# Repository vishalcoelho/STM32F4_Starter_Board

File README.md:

# STM32F4_Starter_Board
KiCAD 9 project for the STM32F405RGT6 starter board

---

I have been following [Phil's Lab Tutorial](https://www.youtube.com/watch?v=C7-8nUU6e3E) on designing your first PCB in KiCad and using JLCPCB as the assembly house. I did the entire project in KiCAD 9, which differs slightly from the video, and ended up taking notes :memo: and screenshots :camera: along the way, which I put into a four part blog:

1. :triangular_ruler: [First STM32 PCB Design in KiCad and JLCPCB Assembly: Part I - Schematic Layout](https://vishalcoelho.github.io/blog/kicad/pcb-design/kicad-stm32-usb-pcb-design-jlcpcb-assy-part-1/)
2. :world_map: [First STM32 PCB Design in KiCad and JLCPCB Assembly: Part II - Board Layout](https://vishalcoelho.github.io/blog/kicad/pcb-design/kicad-stm32-usb-pcb-design-jlcpcb-assy-part-2/)
3. :traffic_light: [First STM32 PCB Design in KiCad and JLCPCB Assembly: Part III - Routing](https://vishalcoelho.github.io/blog/kicad/pcb-design/kicad-stm32-usb-pcb-design-jlcpcb-assy-part-3/)
4. :factory: [First STM32 PCB Design in KiCad and JLCPCB Assembly: Part IV - Manufacturing and Assembly](https://vishalcoelho.github.io/blog/kicad/pcb-design/kicad-stm32-usb-pcb-design-jlcpcb-assy-part-4/)

> :pray: Apologies if the blog doesn't read like a normal tutorial, they really were notes I took for later reference.

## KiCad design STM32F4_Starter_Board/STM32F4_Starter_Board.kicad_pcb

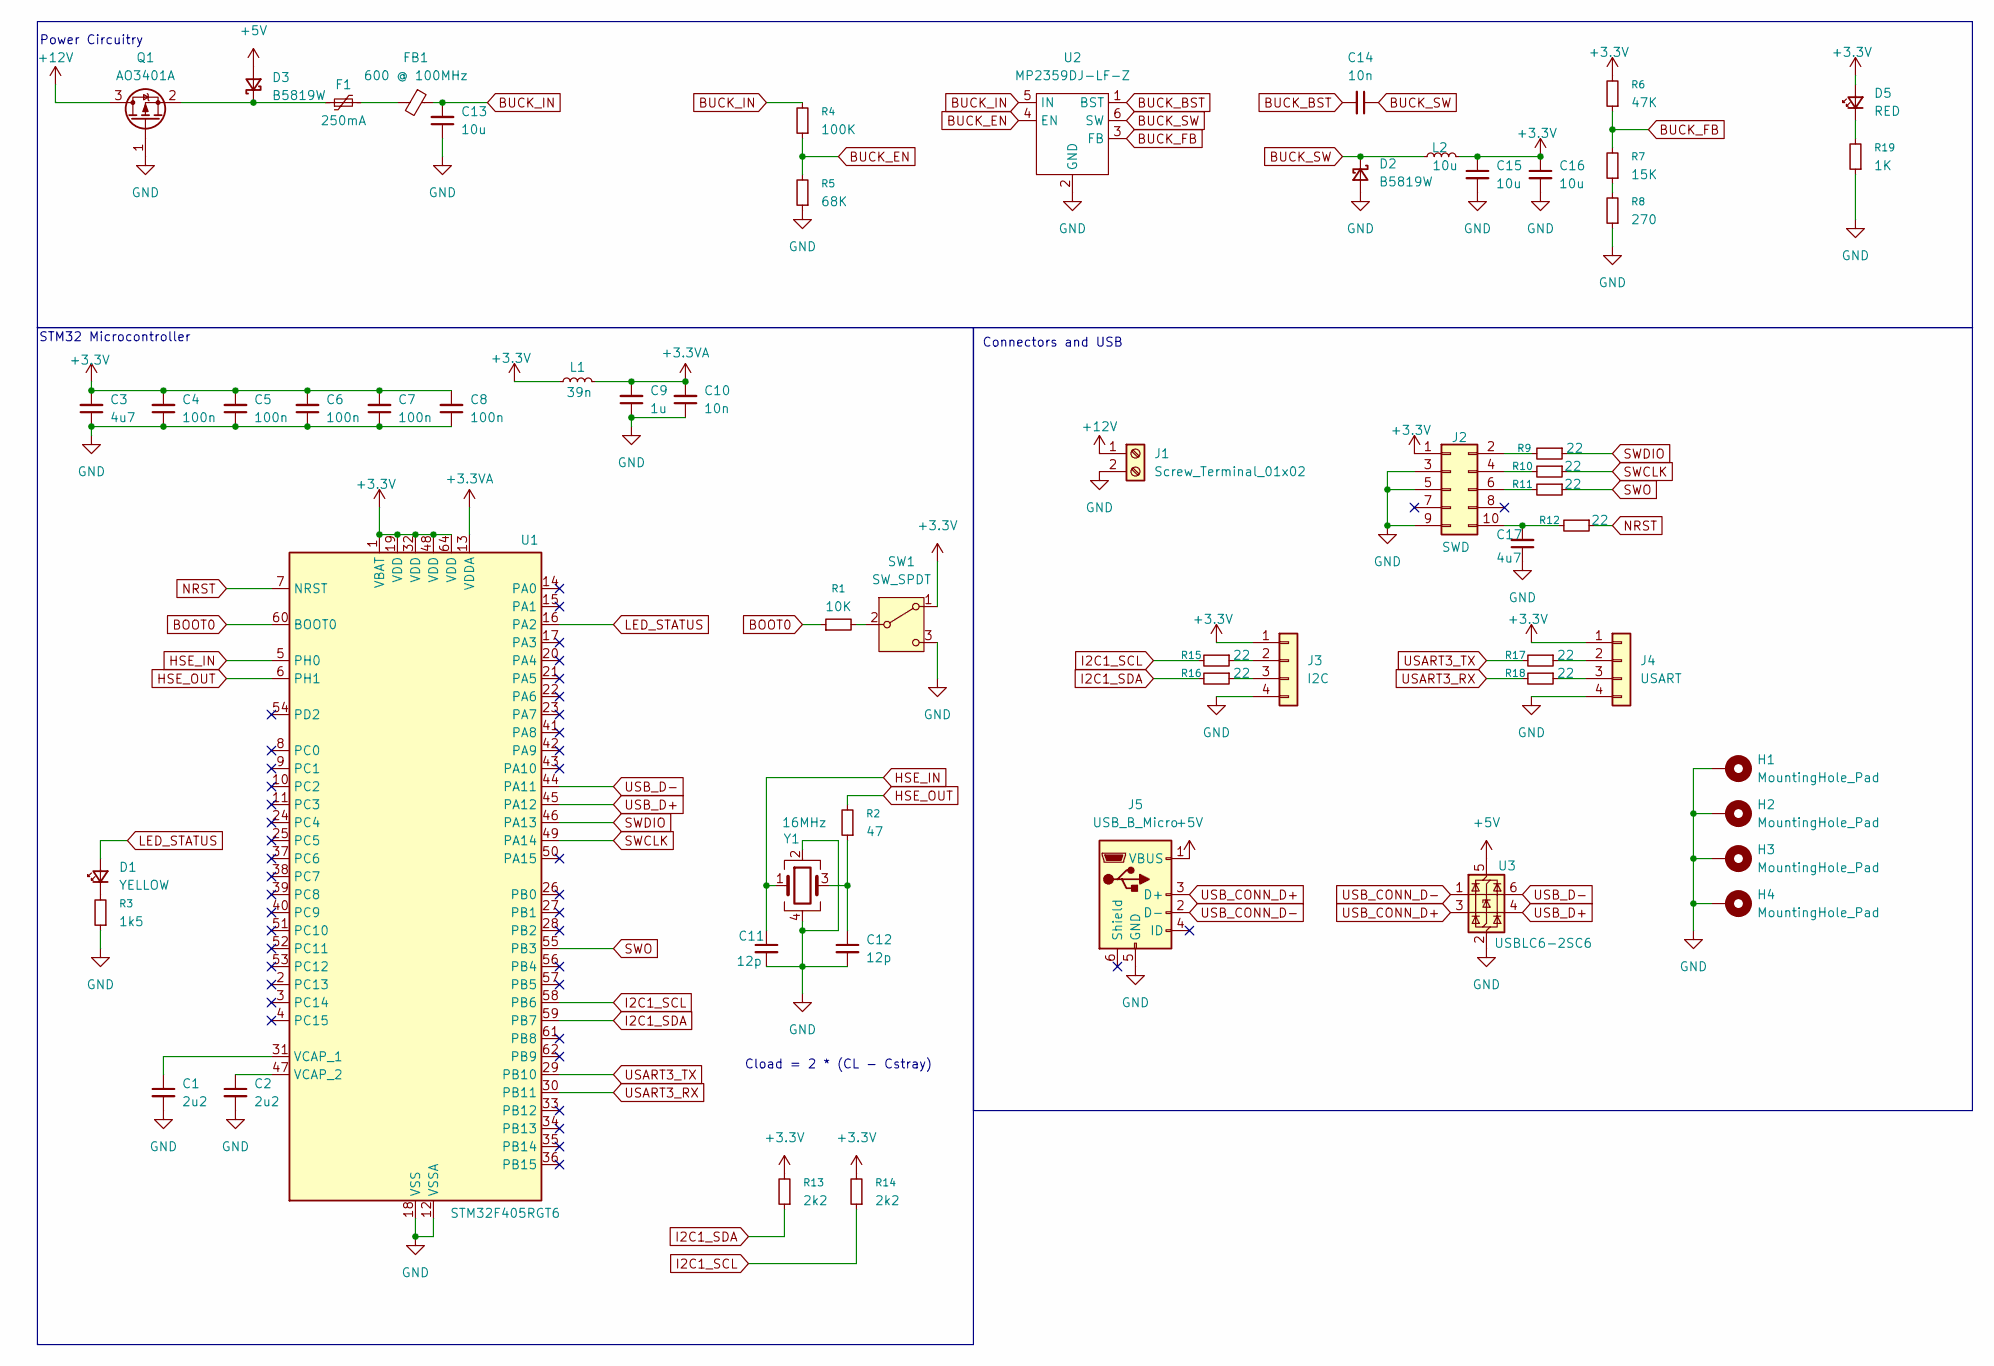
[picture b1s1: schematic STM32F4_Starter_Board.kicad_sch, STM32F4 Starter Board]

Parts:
C1, C2: 2u2; C_0603_1608Metric; JLCPCB Part # C23630
C3, C17: 4u7; C_0603_1608Metric; JLCPCB Part # C19666
C4, C5, C6, C7, C8: 100n; C_0402_1005Metric; JLCPCB Part # C1525
C9: 1u; C_0402_1005Metric; JLCPCB Part # C52923
C10: 10n; C_0603_1608Metric; JLCPCB Part # C57112
C11, C12: 12p; C_0402_1005Metric; JLCPCB Part # C1547
C13, C15, C16: 10u; D_1206_3216Metric; JLCPCB Part # C13585
C14: 10n; D_1206_3216Metric; JLCPCB Part # C1846
D1: YELLOW; LED_0603_1608Metric; JLCPCB Part # C2290
D2, D3: B5819W; D_SOD-123; JLCPCB Part # C8598
D5: RED; LED_0603_1608Metric; JLCPCB Part # C2286
F1: 250mA; Fuse_1206_3216Metric; JLCPCB Part # C83557
FB1: 600 @ 100MHz; L_0805_2012Metric; JLCPCB Part # C1017
H1, H2, H3, H4: MountingHole_Pad; MountingHole_4.3mm_M4_Pad_Via
J1: Screw_Terminal_01x02; TerminalBlock_Phoenix_PT-1,5-2-3.5-H_1x02_P3.50mm_Horizontal; JLCPCB Part # C415432
J2: SWD; PinHeader_2x05_P1.27mm_Vertical_SMD; JLCPCB Part # C4943297
J3: I2C; Molex_PicoBlade_53048-0410_1x04_P1.25mm_Horizontal; JLCPCB Part # C588275
J4: USART; Molex_PicoBlade_53048-0410_1x04_P1.25mm_Horizontal; JLCPCB Part # C588275
J5: USB_B_Micro; USB_Micro-B_Molex_47346-0001; JLCPCB Part # C132560
L1: 39n; L_0402_1005Metric; JLCPCB Part # C26443
L2: 10u; L_Sunlord_MWSA0518S; JLCPCB Part # C408349
Q1: AO3401A; SOT-23; JLCPCB Part # C15127
R1: 10K; R_0402_1005Metric; JLCPCB Part # C25744
R2: 47; R_0402_1005Metric; JLCPCB Part # C23182
R3: 1k5; R_0603_1608Metric; JLCPCB Part # C22843
R4: 100K; R_0603_1608Metric; JLCPCB Part # C25803
R5: 68K; R_0603_1608Metric; JLCPCB Part # C177284
R6: 47K; R_0603_1608Metric; JLCPCB Part # C25819
R7: 15K; R_0603_1608Metric; JLCPCB Part # C22809
R8: 270; R_0603_1608Metric; JLCPCB Part # C22966
R9, R10, R11, R12, R15, R16, R17, R18: 22; R_0402_1005Metric; JLCPCB Part # C23345
R13, R14: 2k2; R_0603_1608Metric; JLCPCB Part # C4190
R19: 1K; R_0603_1608Metric; JLCPCB Part # C21190
SW1: SW_SPDT; SW_SPDT_PCM12; JLCPCB Part # C221841
U1: STM32F405RGT6; LQFP-64_10x10mm_P0.5mm; JLCPCB Part # C15742
U2: MP2359BJ-LF-Z; SOT-23-6; JLCPCB Part # C14259
U3: USBLC6-2SC6; SOT-23-6; JLCPCB Part # C7519
Y1: 16MHz; Crystal_SMD_3225-4Pin_3.2x2.5mm; JLCPCB Part # C13738

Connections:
+3.3V: C3.2, C4.2, C5.2, C6.2, C7.2, C8.2, C15.1, C16.1, D5.2 (A), J2.1, J3.1, J4.1, L1.1, L2.2, R6.2, R13.2, R14.2, SW1.1 (A), U1.1 (VBAT), U1.19 (VDD), U1.32 (VDD), U1.48 (VDD), U1.64 (VDD)
+3.3VA: C9.2, C10.2, L1.2, U1.13 (VDDA)
+5V: D3.2 (A), J5.1 (VBUS), U3.5 (VBUS)
+12V: J1.1, Q1.3 (D)
BOOT0: R1.1, U1.60 (BOOT0)
BUCK_BST: C14.2, U2.1 (BST)
BUCK_EN: R4.1, R5.2, U2.4 (EN)
BUCK_FB: R6.1, R7.2, U2.3 (FB)
BUCK_IN: C13.2, FB1.1, R4.2, U2.5 (IN)
BUCK_SW: C14.1, D2.1 (K), L2.1, U2.6 (SW)
GND: C1.2, C2.2, C3.1, C4.1, C5.1, C6.1, C7.1, C8.1, C9.1, C10.1, C11.2, C12.2, C13.1, C15.2, C16.2, C17.1, D2.2 (A), H1.1, H2.1, H3.1, H4.1, J1.2, J2.3, J2.5, J2.9, J3.4, J4.4, J5.5 (GND), Q1.1 (G), R3.1, R5.1, R8.1, R19.1, SW1.3 (C), U1.12 (VSSA), U1.18 (VSS), U1.63 (VSS), U2.2 (GND), U3.2 (GND), Y1.2, Y1.4
HSE_IN: C11.1, U1.5 (PH0), Y1.1
HSE_OUT: R2.2, U1.6 (PH1)
I2C1_SCL: R14.1, R15.2, U1.58 (PB6)
I2C1_SDA: R13.1, R16.2, U1.59 (PB7)
LED_STATUS: D1.2 (A), U1.16 (PA2)
NRST: R12.1, U1.7 (NRST)
unnamed: C12.1, R2.1, Y1.3
unnamed: D1.1 (K), R3.2
unnamed: D3.1 (K), F1.1, Q1.2 (S)
unnamed: D5.1 (K), R19.2
unnamed: F1.2, FB1.2
unnamed: J2.2, R9.2
unnamed: J2.4, R10.2
unnamed: J2.6, R11.2
unnamed: C17.2, J2.10, R12.2
unnamed: J3.2, R15.1
unnamed: J3.3, R16.1
unnamed: J4.2, R17.1
unnamed: J4.3, R18.1
unnamed: R7.1, R8.2
unnamed: R1.2, SW1.2 (B)
unnamed: C1.1, U1.31 (VCAP_1)
unnamed: C2.1, U1.47 (VCAP_2)
SWCLK: R10.1, U1.49 (PA14)
SWDIO: R9.1, U1.46 (PA13)
SWO: R11.1, U1.55 (PB3)
USART3_RX: R18.2, U1.30 (PB11)
USART3_TX: R17.2, U1.29 (PB10)
USB_CONN_D+: J5.3 (D+), U3.3 (I/O2)
USB_CONN_D-: J5.2 (D-), U3.1 (I/O1)
USB_D+: U1.45 (PA12), U3.4 (I/O2)
USB_D-: U1.44 (PA11), U3.6 (I/O1)

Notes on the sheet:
Cload = 2 * (CL - Cstray)
STM32 Microcontroller
Power Circuitry
Connectors and USB

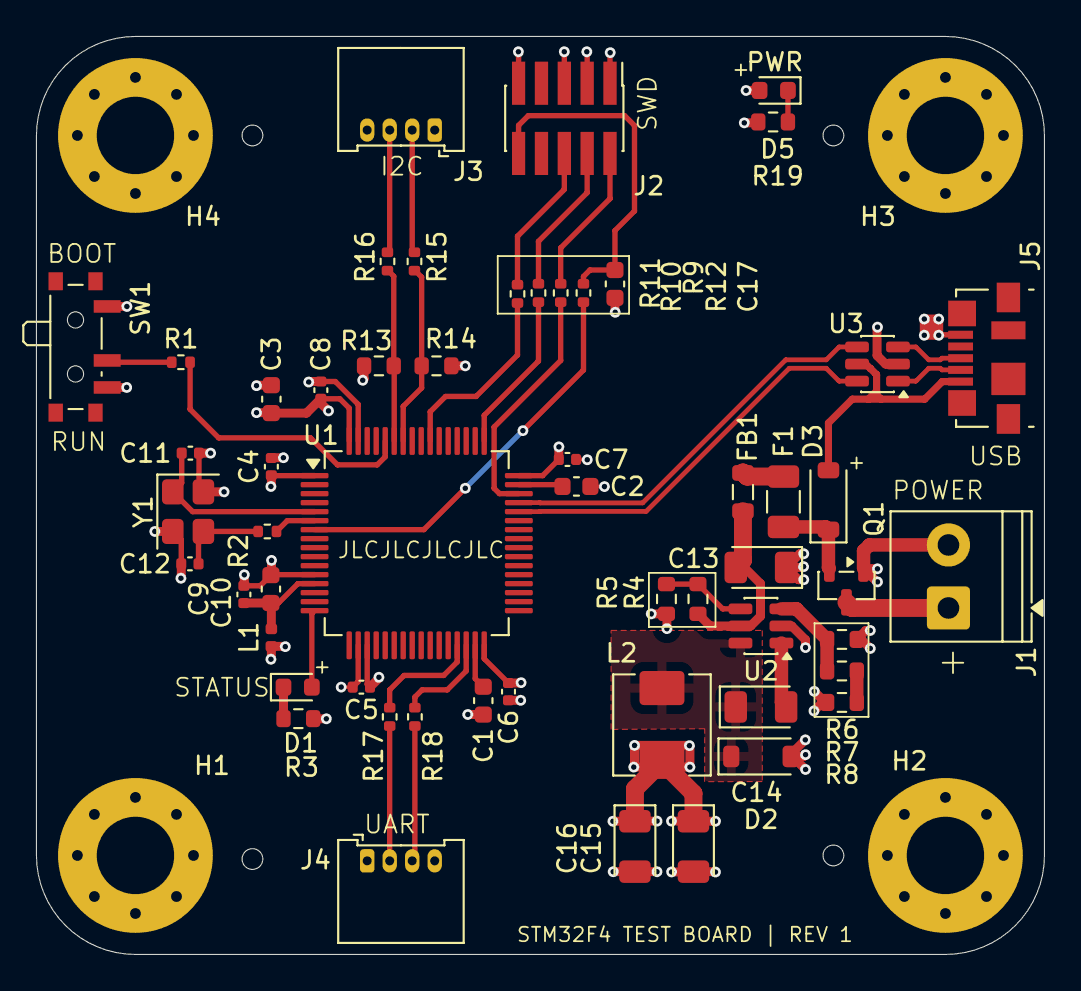
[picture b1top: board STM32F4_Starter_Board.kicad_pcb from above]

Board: 4 copper layers, 56.0 x 51.0 mm, 59 parts (0 on the bottom side), 43 nets.

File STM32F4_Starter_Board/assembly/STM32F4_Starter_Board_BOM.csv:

Comment,Designator,Footprint,JLCPCB Part # (optional)
"2u2","C1,C2","Capacitor_SMD:C_0603_1608Metric","C23630"
"4u7","C3,C17","Capacitor_SMD:C_0603_1608Metric","C19666"
"100n","C4,C5,C6,C7,C8","Capacitor_SMD:C_0402_1005Metric","C1525"
"1u","C9","Capacitor_SMD:C_0402_1005Metric","C52923"
"10n","C10","Capacitor_SMD:C_0603_1608Metric","C57112"
"12p","C11,C12","Capacitor_SMD:C_0402_1005Metric","C1547"
"10u","C13,C15,C16","Diode_SMD:D_1206_3216Metric","C13585 "
"10n","C14","Diode_SMD:D_1206_3216Metric","C1846"
"YELLOW","D1","LED_SMD:LED_0603_1608Metric","C2290"
"B5819W","D2,D3","Diode_SMD:D_SOD-123","C8598"
"RED","D5","LED_SMD:LED_0603_1608Metric","C2286"
"250mA","F1","Fuse:Fuse_1206_3216Metric","C83557"
"600 @ 100MHz","FB1","Inductor_SMD:L_0805_2012Metric","C1017"
"Screw_Terminal_01x02","J1","TerminalBlock_Phoenix:TerminalBlock_Phoenix_PT-1,5-2-3.5-H_1x02_P3.50mm_Horizontal","C415432"
"SWD","J2","Connector_PinHeader_1.27mm:PinHeader_2x05_P1.27mm_Vertical_SMD","C4943297"
"I2C","J3","Connector_Molex:Molex_PicoBlade_53048-0410_1x04_P1.25mm_Horizontal","C588275"
"USART","J4","Connector_Molex:Molex_PicoBlade_53048-0410_1x04_P1.25mm_Horizontal","C588275"
"USB_B_Micro","J5","Connector_USB:USB_Micro-B_Molex_47346-0001","C132560"
"39n","L1","Inductor_SMD:L_0402_1005Metric","C26443"
"10u","L2","Inductor_SMD:L_Sunlord_MWSA0518S","C408349"
"AO3401A","Q1","Package_TO_SOT_SMD:SOT-23","C15127"
"10K","R1","Resistor_SMD:R_0402_1005Metric","C25744"
"47","R2","Resistor_SMD:R_0402_1005Metric","C23182"
"1k5","R3","Resistor_SMD:R_0603_1608Metric","C22843 "
"100K","R4","Resistor_SMD:R_0603_1608Metric","C25803"
"68K","R5","Resistor_SMD:R_0603_1608Metric","C177284 "
"47K","R6","Resistor_SMD:R_0603_1608Metric","C25819"
"15K","R7","Resistor_SMD:R_0603_1608Metric","C22809"
"270","R8","Resistor_SMD:R_0603_1608Metric","C22966"
"22","R9,R10,R11,R12,R15,R16,R17,R18","Resistor_SMD:R_0402_1005Metric","C23345"
"2k2","R13,R14","Resistor_SMD:R_0603_1608Metric","C4190"
"1K","R19","Resistor_SMD:R_0603_1608Metric","C21190"
"SW_SPDT","SW1","Button_Switch_SMD:SW_SPDT_PCM12","C221841"
"STM32F405RGT6","U1","Package_QFP:LQFP-64_10x10mm_P0.5mm","C15742"
"MP2359BJ-LF-Z","U2","Package_TO_SOT_SMD:SOT-23-6","C14259"
"USBLC6-2SC6","U3","Package_TO_SOT_SMD:SOT-23-6","C7519"
"16MHz","Y1","Crystal:Crystal_SMD_3225-4Pin_3.2x2.5mm","C13738"

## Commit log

2026-04-06 [KiCAD] Add the KiCAD 9 project files for the STM32F4 Starter Board.
2026-04-06 [KICAD] Force add the asesembly files.
